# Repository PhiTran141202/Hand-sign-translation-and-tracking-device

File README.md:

# **hand-tracking and ASL translation prototype device**

\############################# **INTRODUCTION ##############################**

The project's foundation is based on the mediapipe(https://mediapipe.dev/) Hands recognition repo by Kazuhito Takahashi (https://github.com/Kazuhito00/hand-gesture-recognition-using-mediapipe) and translated into English by Nikita Kiselov (https://github.com/kinivi). For the handtracking part, it is based on the repo by Rizky Dermawan (Rishttps://github.com/rizkydermawan1992/handtracking)

My version of the repo is trained to read 24 letters of the ASL alphabet (minus J and K), integrated the hand tracking function performed by pan and tilt servos, and controlled by an Arduino nano, with added photosensor and LCD screen.

All of these are controlled by a Raspberry Pi 4, which will be processing the captured images with a Picamera attached to the servos. This required more modifications so that the program can work properly in the Raspbian OS and in conjunction with the Picamera and the servos.

The Arduino is powered by a 9V battery, and the Pi is powered by a portable power bank (Output: 5V - 2A, Capacity: 5000mAh)

**Note: Mediapipe doesn't work on Raspbian Bullseye -> download the bookworm version**

**HERE ARE THE STEPS TO MAKE SURE THE MAIN PROGRAM RUNS SMOOTHLY WHEN IMPORTED INTO THE RASPBERRY PI SYSTEM:**

\####################### **Image Processing part** ############################

**STEP 1: setting up the Pi**

* Raspbian OS: Raspberry Pi OS (64bit), Debian Bookworm with desktop
* Python 3.11.2
* Packages: update + upgrade

**STEP 2: using pip3, run these commands**

* sudo rm/usr/lib/python3.11/EXTERNALLY-MANAGED
* sudo pip3 install mediapipe
* sudo pip3 install cvzone (optional)
* sudo pip3 install opencv-python
* sudo apt install python3-dev libhdf5-dev
* sudo apt install libatlas-base-dev
* pip3 install tensorflow
* sudo pip3 install gtts
* sudo apt install mpg321
* sudo pip3 install pyfirmata2 (the normal pyfirmata will not work, trust me i tried)

**STEP 3: Run the prototype.py**

\*CONSULT THE ORIGINAL MEDIAPIPE REPO TO TRAIN YOUR OWN DATA\*

\####################### **Hand tracking part** ############################

**Python packages required for hand tracking:**

* opencv-python 4.5.5.64
* mediapipe 0.8.10
* pyfirmata2

**Arduino Configuration**

* Open IDE Arduino
* Select File -> Example -> Firmata -> StandardFirmata
* Select Tools -> Board -> Arduino/Genuino Uno
* Select Tools -> Port -> *choose your port COM*
* Upload the Arduino codes

\######################### **REFERENCES ###################################**

\*\[MediaPipe](https://mediapipe.dev/)

\# Author

Kazuhito Takahashi(https://twitter.com/KzhtTkhs)

\# Translation and other improvements

Nikita Kiselov(https://github.com/kinivi)

\# License

hand-gesture-recognition-using-mediapipe is under \[Apache v2 license](LICENSE).

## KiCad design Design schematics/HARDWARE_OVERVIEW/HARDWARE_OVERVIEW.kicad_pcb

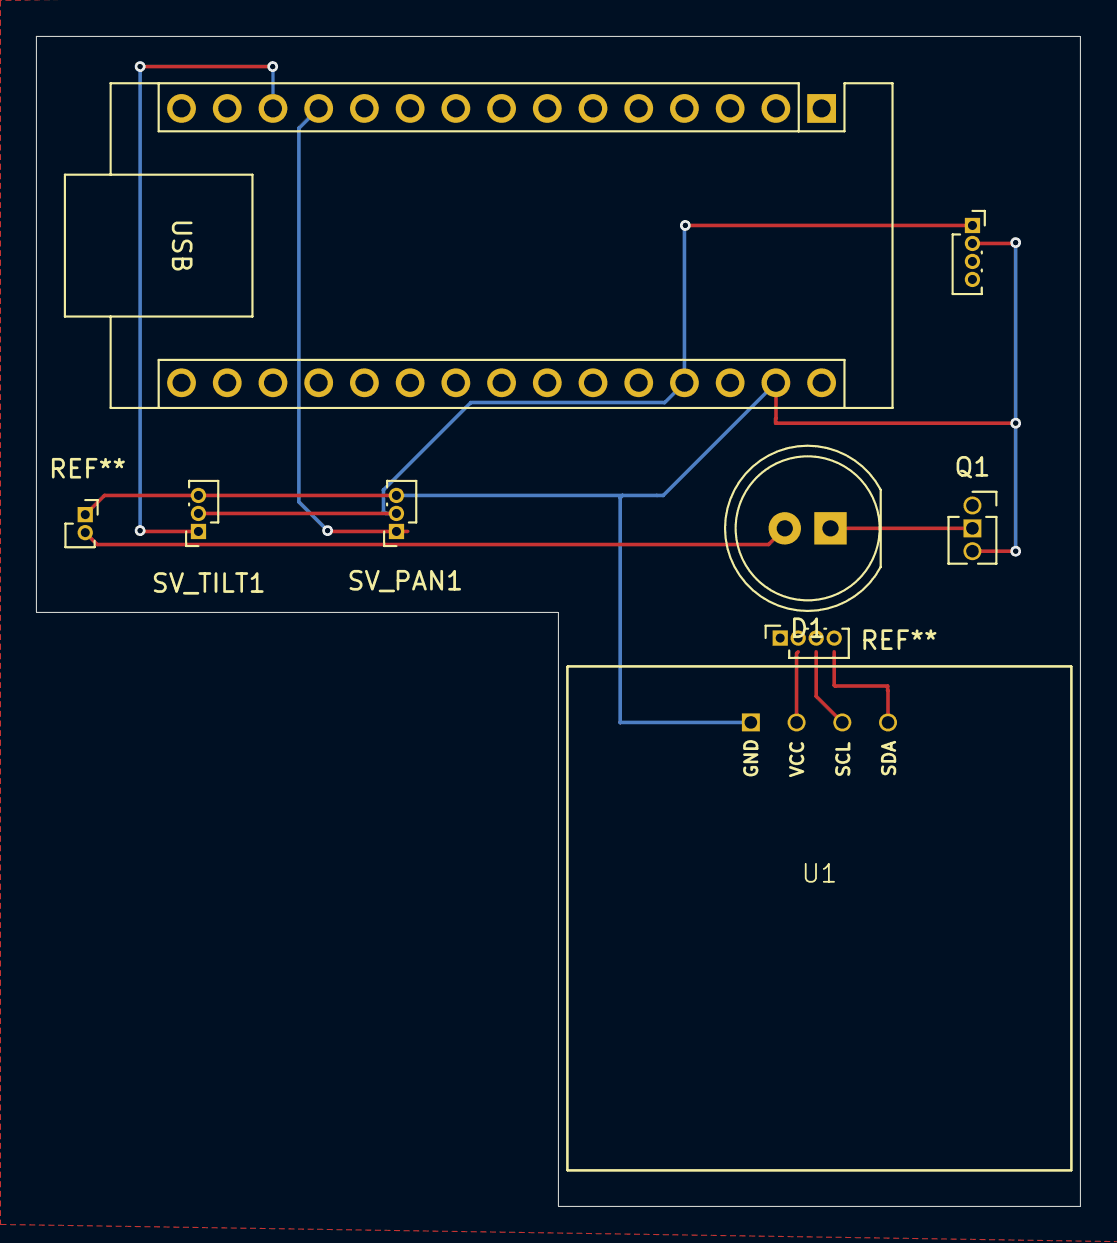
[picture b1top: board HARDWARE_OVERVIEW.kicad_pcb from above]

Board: 2 copper layers, 58.0 x 65.0 mm, 7 parts (0 on the bottom side), 5 nets.

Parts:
A1: Arduino_Nano
D1: LED; LED_D8.0mm
Photoresistor_module1: PinSocket_1x04_P1.00mm_Vertical
Q1: IRF730; PinSocket_1x03_P1.27mm_Vertical
SV_PAN1: Motor_Servo; PinSocket_1x03_P1.00mm_Vertical
SV_TILT1: Motor_Servo; PinSocket_1x03_P1.00mm_Vertical
U1: SSD1306

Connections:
+5V: A1.27 (+5V), Photoresistor_module1.1 (VCC), SV_PAN1.2 (+), SV_TILT1.2 (+)
GND: A1.29 (GND), Photoresistor_module1.2 (GND), Q1.3 (S), SV_PAN1.3 (-), SV_TILT1.3 (-), U1.1 (GND)
unnamed: A1.12 (D9), SV_PAN1.1 (PWM)
unnamed: A1.13 (D10), SV_TILT1.1 (PWM)
unnamed: D1.1 (K), Q1.1 (D)

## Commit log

2026-03-04 README added
2026-03-09 updated instructions
2026-03-15 updated document
2026-04-04 updated instruction
